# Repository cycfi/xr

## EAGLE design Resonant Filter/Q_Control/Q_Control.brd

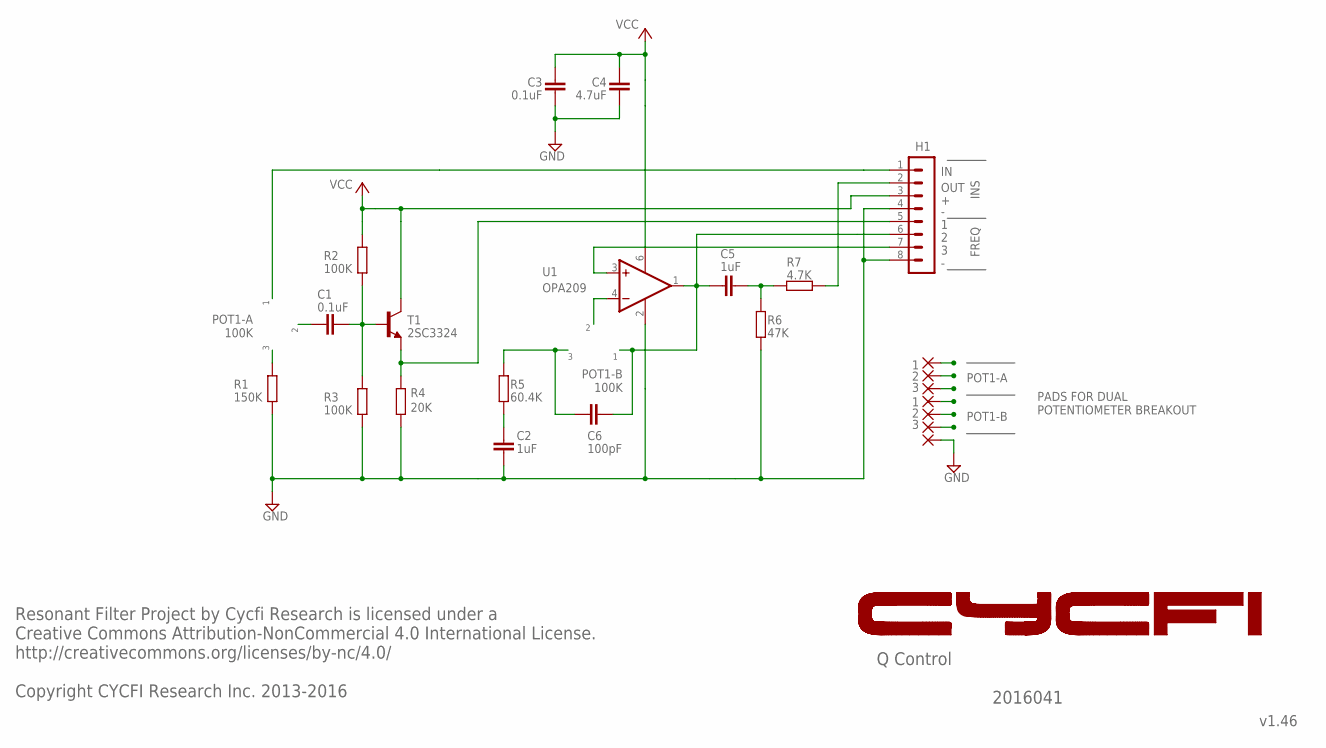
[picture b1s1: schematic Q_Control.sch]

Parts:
C1, C3: 0.1uF; C0603
C2, C5: 1uF; C0805
C4: 4.7uF; C0603
C6: 100pF; C0805
H1: MA08-1
PAD1, PAD2, PAD3, PAD4, PAD5, PAD6, PAD7: SMD2; SMD1,27-2,54
R1: 150K; R0402
R2, R3: 100K; R0402
R4: 20K; R0402
R5: 60.4K; R0402
R6: 47K; R0402
R7: 4.7K; R0402
T1: 2SC3324; SOT23
U1: OPA209; SOT23-6

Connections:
1: H1.5, R4.2, T1.2 (E)
3: H1.7, U1.3 (+IN)
ASDADS: C5.1, R6.2, R7.1
BYP: H1.1, PAD1.1
EQ: H1.2, R7.2
GND: C2.1, C3.1, C4.1, H1.4, H1.8, PAD7.1, R1.1, R3.1, R4.1, R6.1, U1.2 (V-)
INPUT: C1.1, PAD2.1
unnamed: C1.2, R2.1, R3.2, T1.1 (B)
unnamed: C2.2, R5.2
PA-3: PAD3.1, R1.2
PTB-1: C5.2, C6.2, H1.6, PAD5.1, U1.1 (OUT)
PTB-2: PAD6.1, U1.4 (-IN)
PTB-3: C6.1, PAD4.1, R5.1
VIN: C3.2, C4.2, H1.3, R2.2, T1.3 (C), U1.6 (V+)

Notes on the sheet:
OUT
POT1-A 100K
POT1-B 100K
INS
FREQ
POT1-A
POT1-B
PADS FOR DUAL POTENTIOMETER BREAKOUT
Q Control
v1.46
Resonant Filter Project by Cycfi Research is licensed under a Creative Commons Attribution-NonCommercial 4.0 International License. http://creativecommons.org/licenses/by-nc/4.0/ Copyright CYCFI Research Inc. 2013-2016
2016041

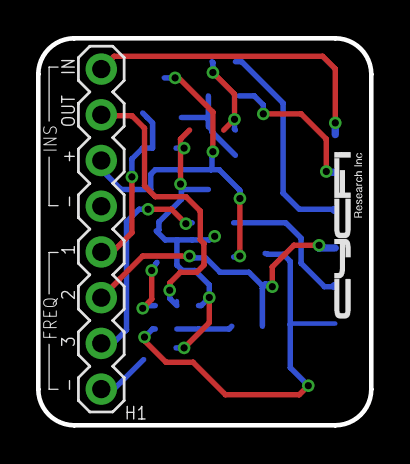
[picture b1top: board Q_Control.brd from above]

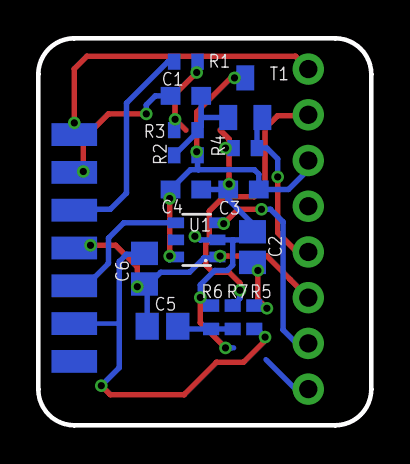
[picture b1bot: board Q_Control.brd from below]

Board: 2 copper layers, 18.5 x 21.5 mm, 23 parts (22 on the bottom side), 14 nets.

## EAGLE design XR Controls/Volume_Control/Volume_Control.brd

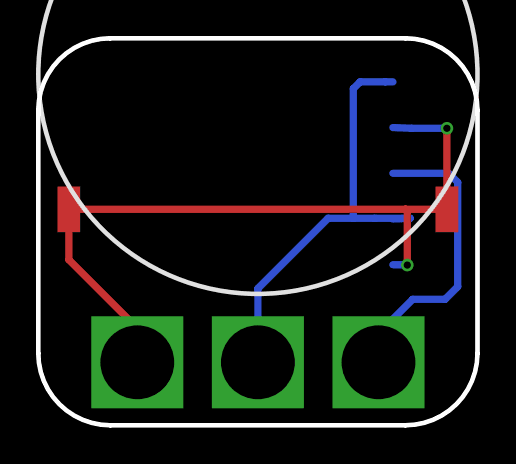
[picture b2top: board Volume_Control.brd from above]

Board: 2 copper layers, 24.4 x 21.5 mm, 4 parts (1 on the bottom side), 3 nets.

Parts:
GND3, GND4: SMD1,27-2,54
H1: 961105-5500-AR-PR; 5P-SMD-2.54MM
POT1: PDB241-GTR01; PDB241

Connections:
GND: GND3.1, GND4.1, H1.P$1, H1.P$4, POT1.P$1
unnamed: H1.P$3, POT1.P$3
unnamed: H1.P$2, H1.P$5, POT1.P$2
